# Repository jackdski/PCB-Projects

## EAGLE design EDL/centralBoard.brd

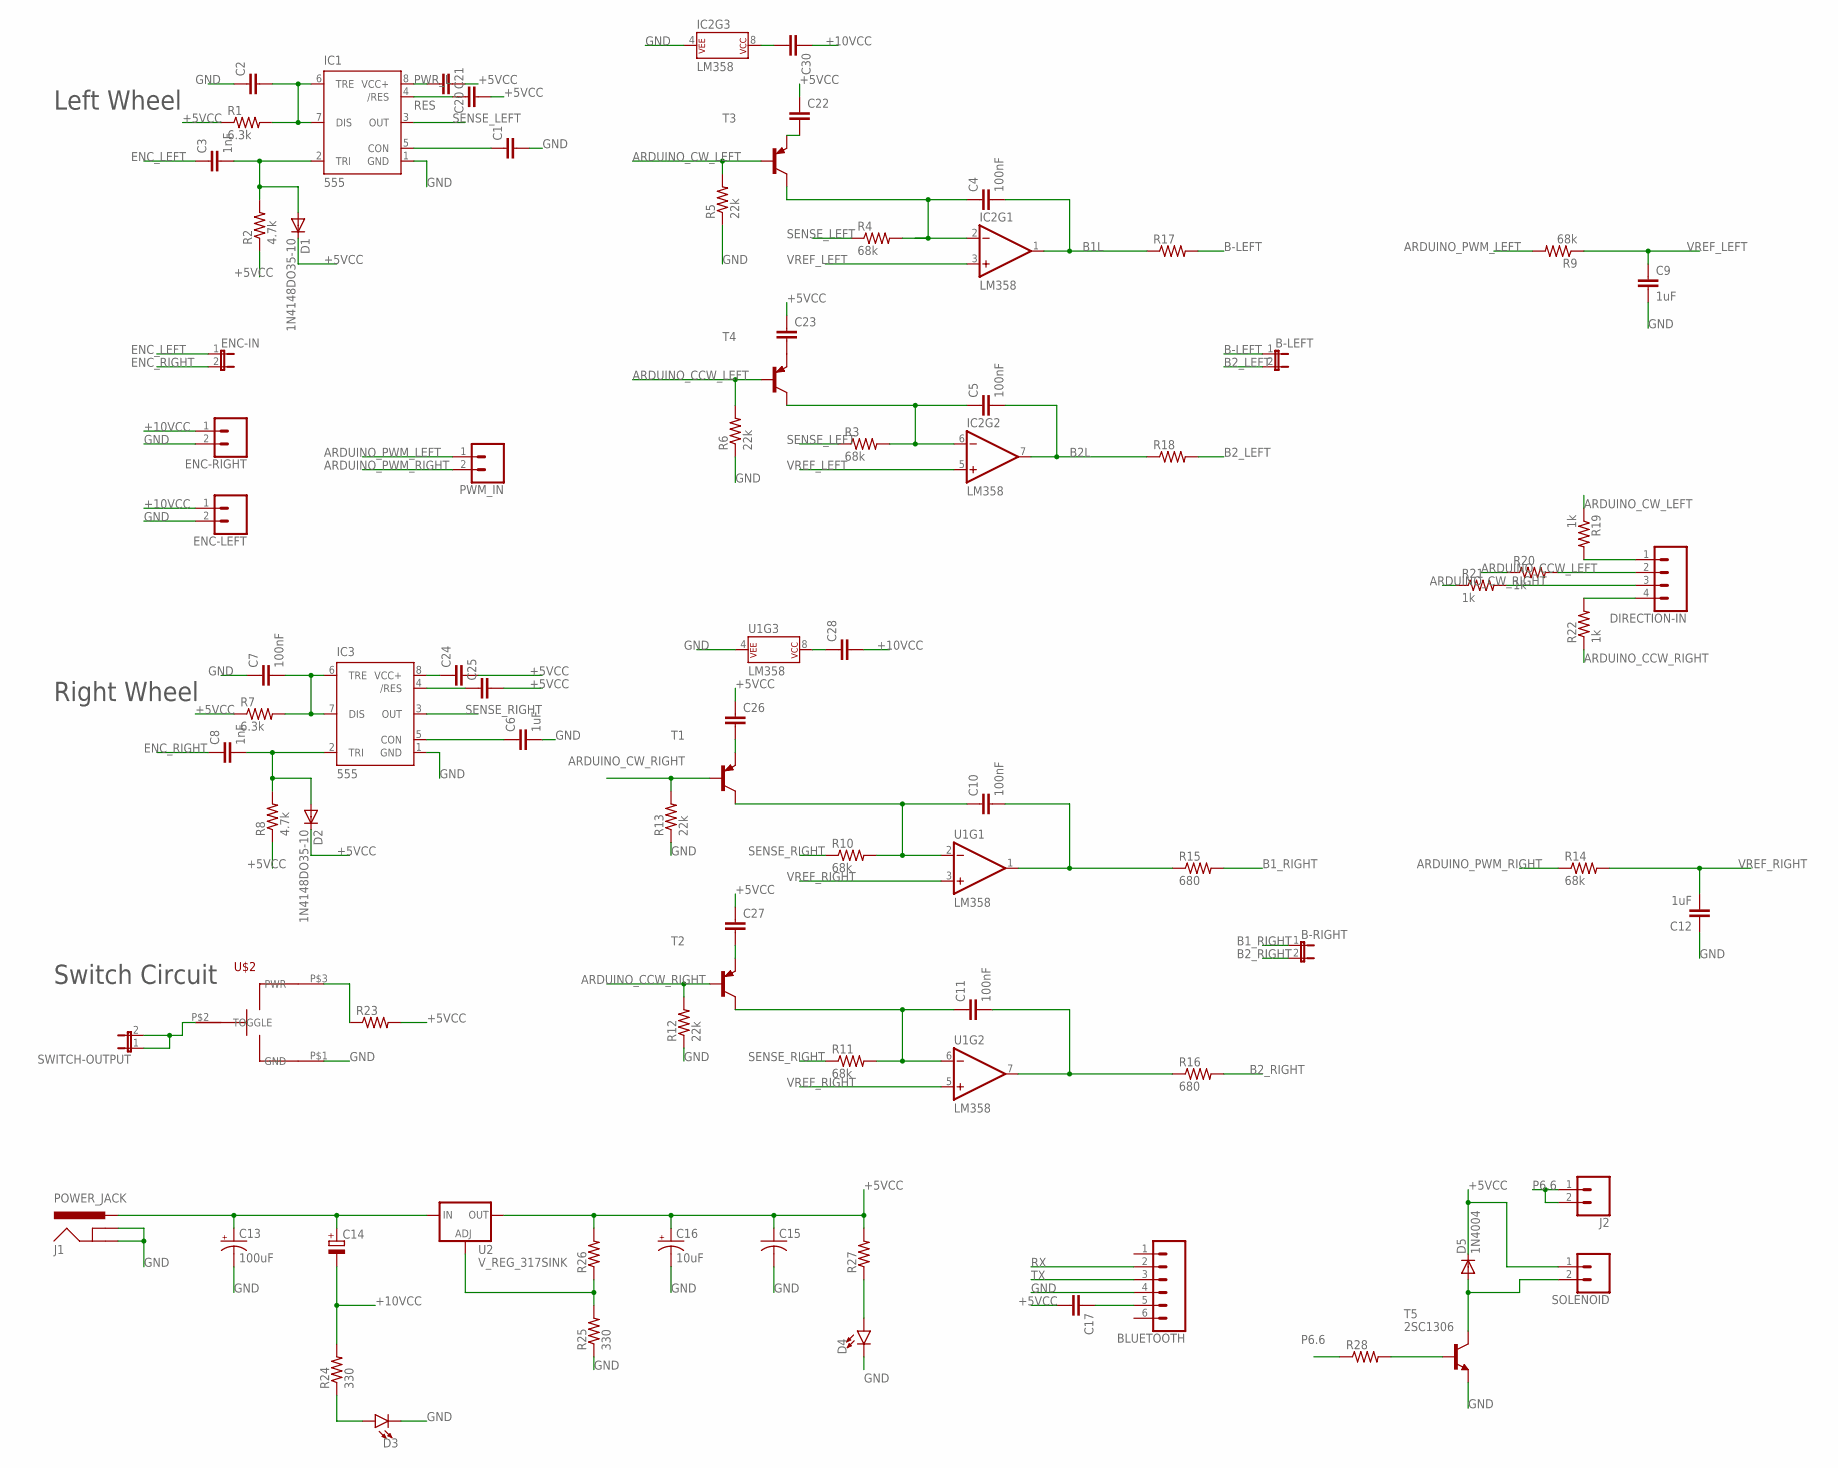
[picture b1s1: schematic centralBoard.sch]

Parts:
B-LEFT: JUMPER-2PTH; 1X02
B-RIGHT: JUMPER-2PTH; 1X02
BLUETOOTH: CONN_06SILK_FEMALE_PTH; 1X06
C1, C2, C20, C21, C22, C23, C24, C25, C26, C27, C28, C30: C5/2.5; C5B2.5
C3, C8: 1nF; C5B2.5
C4, C5, C7, C10, C11: 100nF; C5B2.5
C6, C9, C12: 1uF; C5B2.5
C13: 100uF; CPOL-RADIAL-2.5MM-6.5MM
C14: CPOL-EUE5-6; E5-6
C15: C-US050-030X075; C050-030X075
C16: 10uF; CPOL-RADIAL-2.5MM-5MM
C17: C5/3; C5B3
D1, D2: 1N4148DO35-10; DO35-10
D3, D4: LED-RED1206; LED-1206
D5: 1N4004; DO41-10
DIRECTION-IN: CONN_04; 1X04
ENC-IN: JUMPER-2PTH; 1X02
ENC-LEFT: CONN_02; 1X02
ENC-RIGHT: CONN_02; 1X02
IC1, IC3: 555; DIP08-KIT
IC2: LM358; DIP08
J1: POWER_JACK; POWER_JACK_PTH
J2: CONN_02; 1X02
PWM_IN: CONN_02LOCK; 1X02_LOCK
R1, R7: 6.3k; 0207/10
R2, R8: 4.7k; 0207/10
R3, R4, R9, R10, R11, R14: 68k; 0207/10
R5, R6, R12, R13: 22k; 0207/10
R15, R16: 680; 0207/10
R17, R18, R23, R26, R27, R28: R-US_0207/10; 0207/10
R19, R20, R21, R22: 1k; 0207/10
R24, R25: 330; 0207/10
SOLENOID: CONN_02; 1X02
SWITCH-OUTPUT: JUMPER-2PTH; 1X02
T1, T2, T3, T4: 2N4126-PNP-TO92-CBE; TO92-CBE
T5: 2SC1306; TO220BV
U1: LM358; DIP08
U2: V_REG_317SINK; TO220-ADJ
U$2: SWITCH

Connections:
+5VCC: C15.1, C16.1 (+), C17.2, C20.1, C21.2, C22.1, C23.1, C24.2, C25.2, C26.1, C27.1, D1.C, D2.C, D5.C, R1.1, R2.1, R7.1, R8.1, R23.2, R26.2, R27.2, SOLENOID.1, U2.OUT
+10VCC: C14.-, C28.2, C30.1, ENC-LEFT.1, ENC-RIGHT.1, R24.2
ARDUINO_CCW_LEFT: R6.2, R20.1, T4.B
ARDUINO_CCW_RIGHT: R12.2, R22.1, T2.B
ARDUINO_CW_LEFT: R5.2, R19.1, T3.B
ARDUINO_CW_RIGHT: R13.2, R21.1, T1.B
ARDUINO_PWM_LEFT: PWM_IN.1, R9.2
ARDUINO_PWM_RIGHT: PWM_IN.2, R14.1
B1L: C4.2, IC2.1 (OUT), R17.1
B1R: C10.2, R15.1, U1.1 (OUT)
B1_RIGHT: B-RIGHT.1, R15.2
B2L: C5.2, IC2.7 (OUT), R18.1
B2R: C11.2, R16.1, U1.7 (OUT)
B2_LEFT: B-LEFT.2, R18.2
B2_RIGHT: B-RIGHT.2, R16.2
B-LEFT: B-LEFT.1, R17.2
ENC_LEFT: C3.1, ENC-IN.1
ENC_RIGHT: C8.1, ENC-IN.2
GND: BLUETOOTH.4, C1.2, C2.1, C6.2, C7.1, C9.2, C12.1, C13.2 (-), C15.2, C16.2 (-), D3.C, D4.C, ENC-LEFT.2, ENC-RIGHT.2, IC1.1 (GND), IC2.4 (P$V-), IC3.1 (GND), J1.GND, J1.GNDBREAK, R5.1, R6.1, R12.1, R13.1, R25.1, T5.3 (E), U1.4 (P$V-), U$2.P$1 (GND)
unnamed: C1.1, IC1.5 (CON)
unnamed: C22.2, T3.E
unnamed: C4.1, IC2.2 (-IN), R4.2, T3.C
unnamed: C2.2, IC1.6 (TRE), IC1.7 (DIS), R1.2
unnamed: C23.2, T4.E
unnamed: C5.1, IC2.6 (-IN), R3.2, T4.C
unnamed: C3.2, D1.A, IC1.2 (TRI), R2.2
unnamed: C10.1, R10.2, T1.C, U1.2 (-IN)
unnamed: C24.1, IC3.8 (VCC+)
unnamed: C26.2, T1.E
unnamed: C6.1, IC3.5 (CON)
unnamed: C7.2, IC3.6 (TRE), IC3.7 (DIS), R7.2
unnamed: C8.2, D2.A, IC3.2 (TRI), R8.2
unnamed: C11.1, R11.2, T2.C, U1.6 (-IN)
unnamed: C30.2, IC2.8 (P$V+)
unnamed: DIRECTION-IN.1, R19.2
unnamed: DIRECTION-IN.2, R20.2
unnamed: DIRECTION-IN.3, R21.2
unnamed: DIRECTION-IN.4, R22.2
unnamed: C27.2, T2.E
unnamed: C25.1, IC3.4 (/RES)
unnamed: C13.1 (+), C14.+, J1.PWR, U2.IN
unnamed: R23.1, U$2.P$3 (PWR)
unnamed: C28.1, U1.8 (P$V+)
unnamed: D4.A, R27.1
unnamed: R25.2, R26.1, U2.ADJ
unnamed: SWITCH-OUTPUT.1, SWITCH-OUTPUT.2, U$2.P$2 (TOGGLE)
unnamed: D3.A, R24.1
unnamed: BLUETOOTH.5, C17.1
unnamed: R28.2, T5.1 (B)
unnamed: D5.A, SOLENOID.2, T5.2 (C)
P6.6: J2.1, J2.2, R28.1
PWR_L: C20.2, IC1.8 (VCC+)
RES: C21.1, IC1.4 (/RES)
RX: BLUETOOTH.2
SENSE_LEFT: IC1.3 (OUT), R3.1, R4.1
SENSE_RIGHT: IC3.3 (OUT), R10.1, R11.1
TX: BLUETOOTH.3
VREF_LEFT: C9.1, IC2.3 (+IN), IC2.5 (+IN), R9.1
VREF_RIGHT: C12.2, R14.2, U1.3 (+IN), U1.5 (+IN)

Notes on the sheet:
Right Wheel
Left Wheel
Switch Circuit

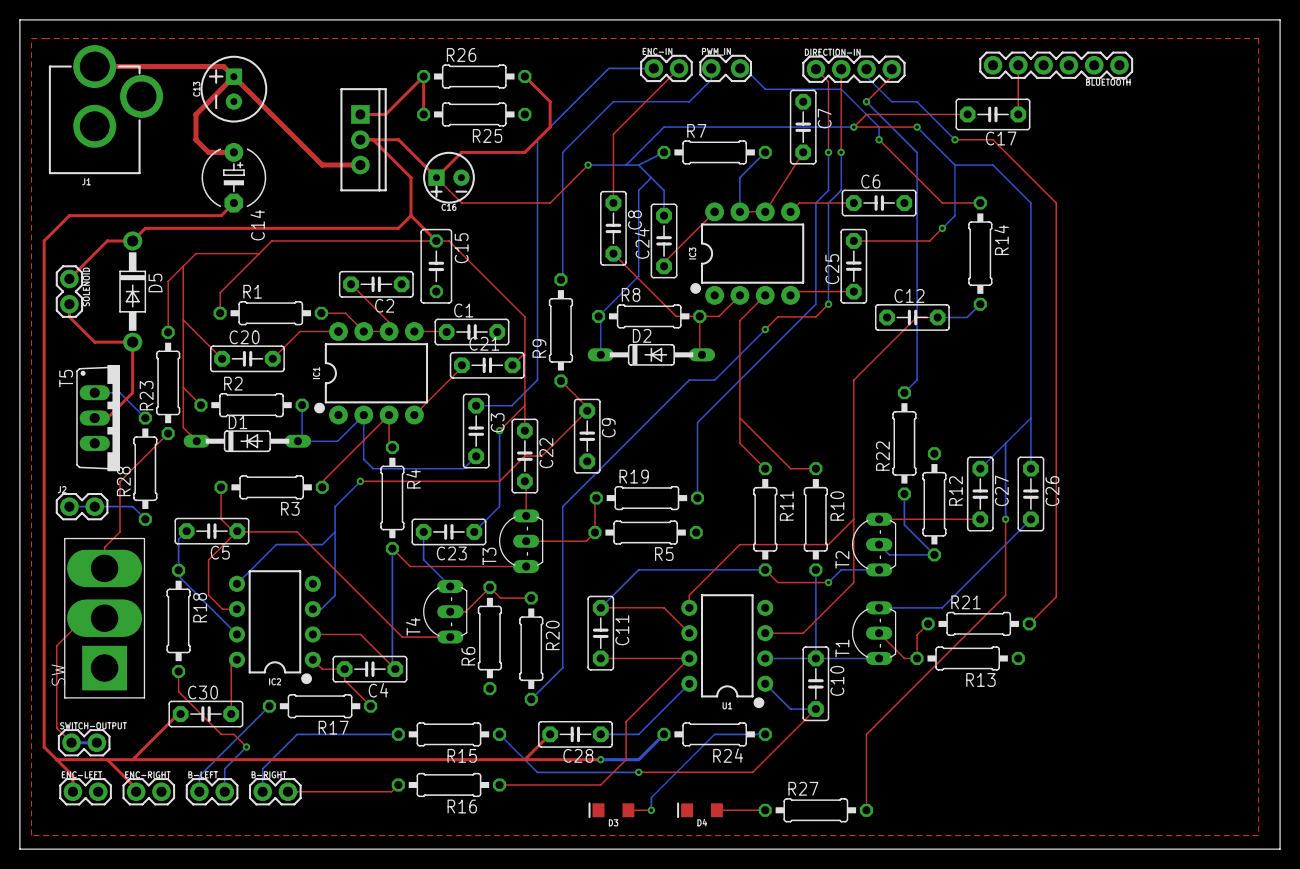
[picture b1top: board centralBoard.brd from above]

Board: 2 copper layers, 126.5 x 83.2 mm, 83 parts (0 on the bottom side), 57 nets.

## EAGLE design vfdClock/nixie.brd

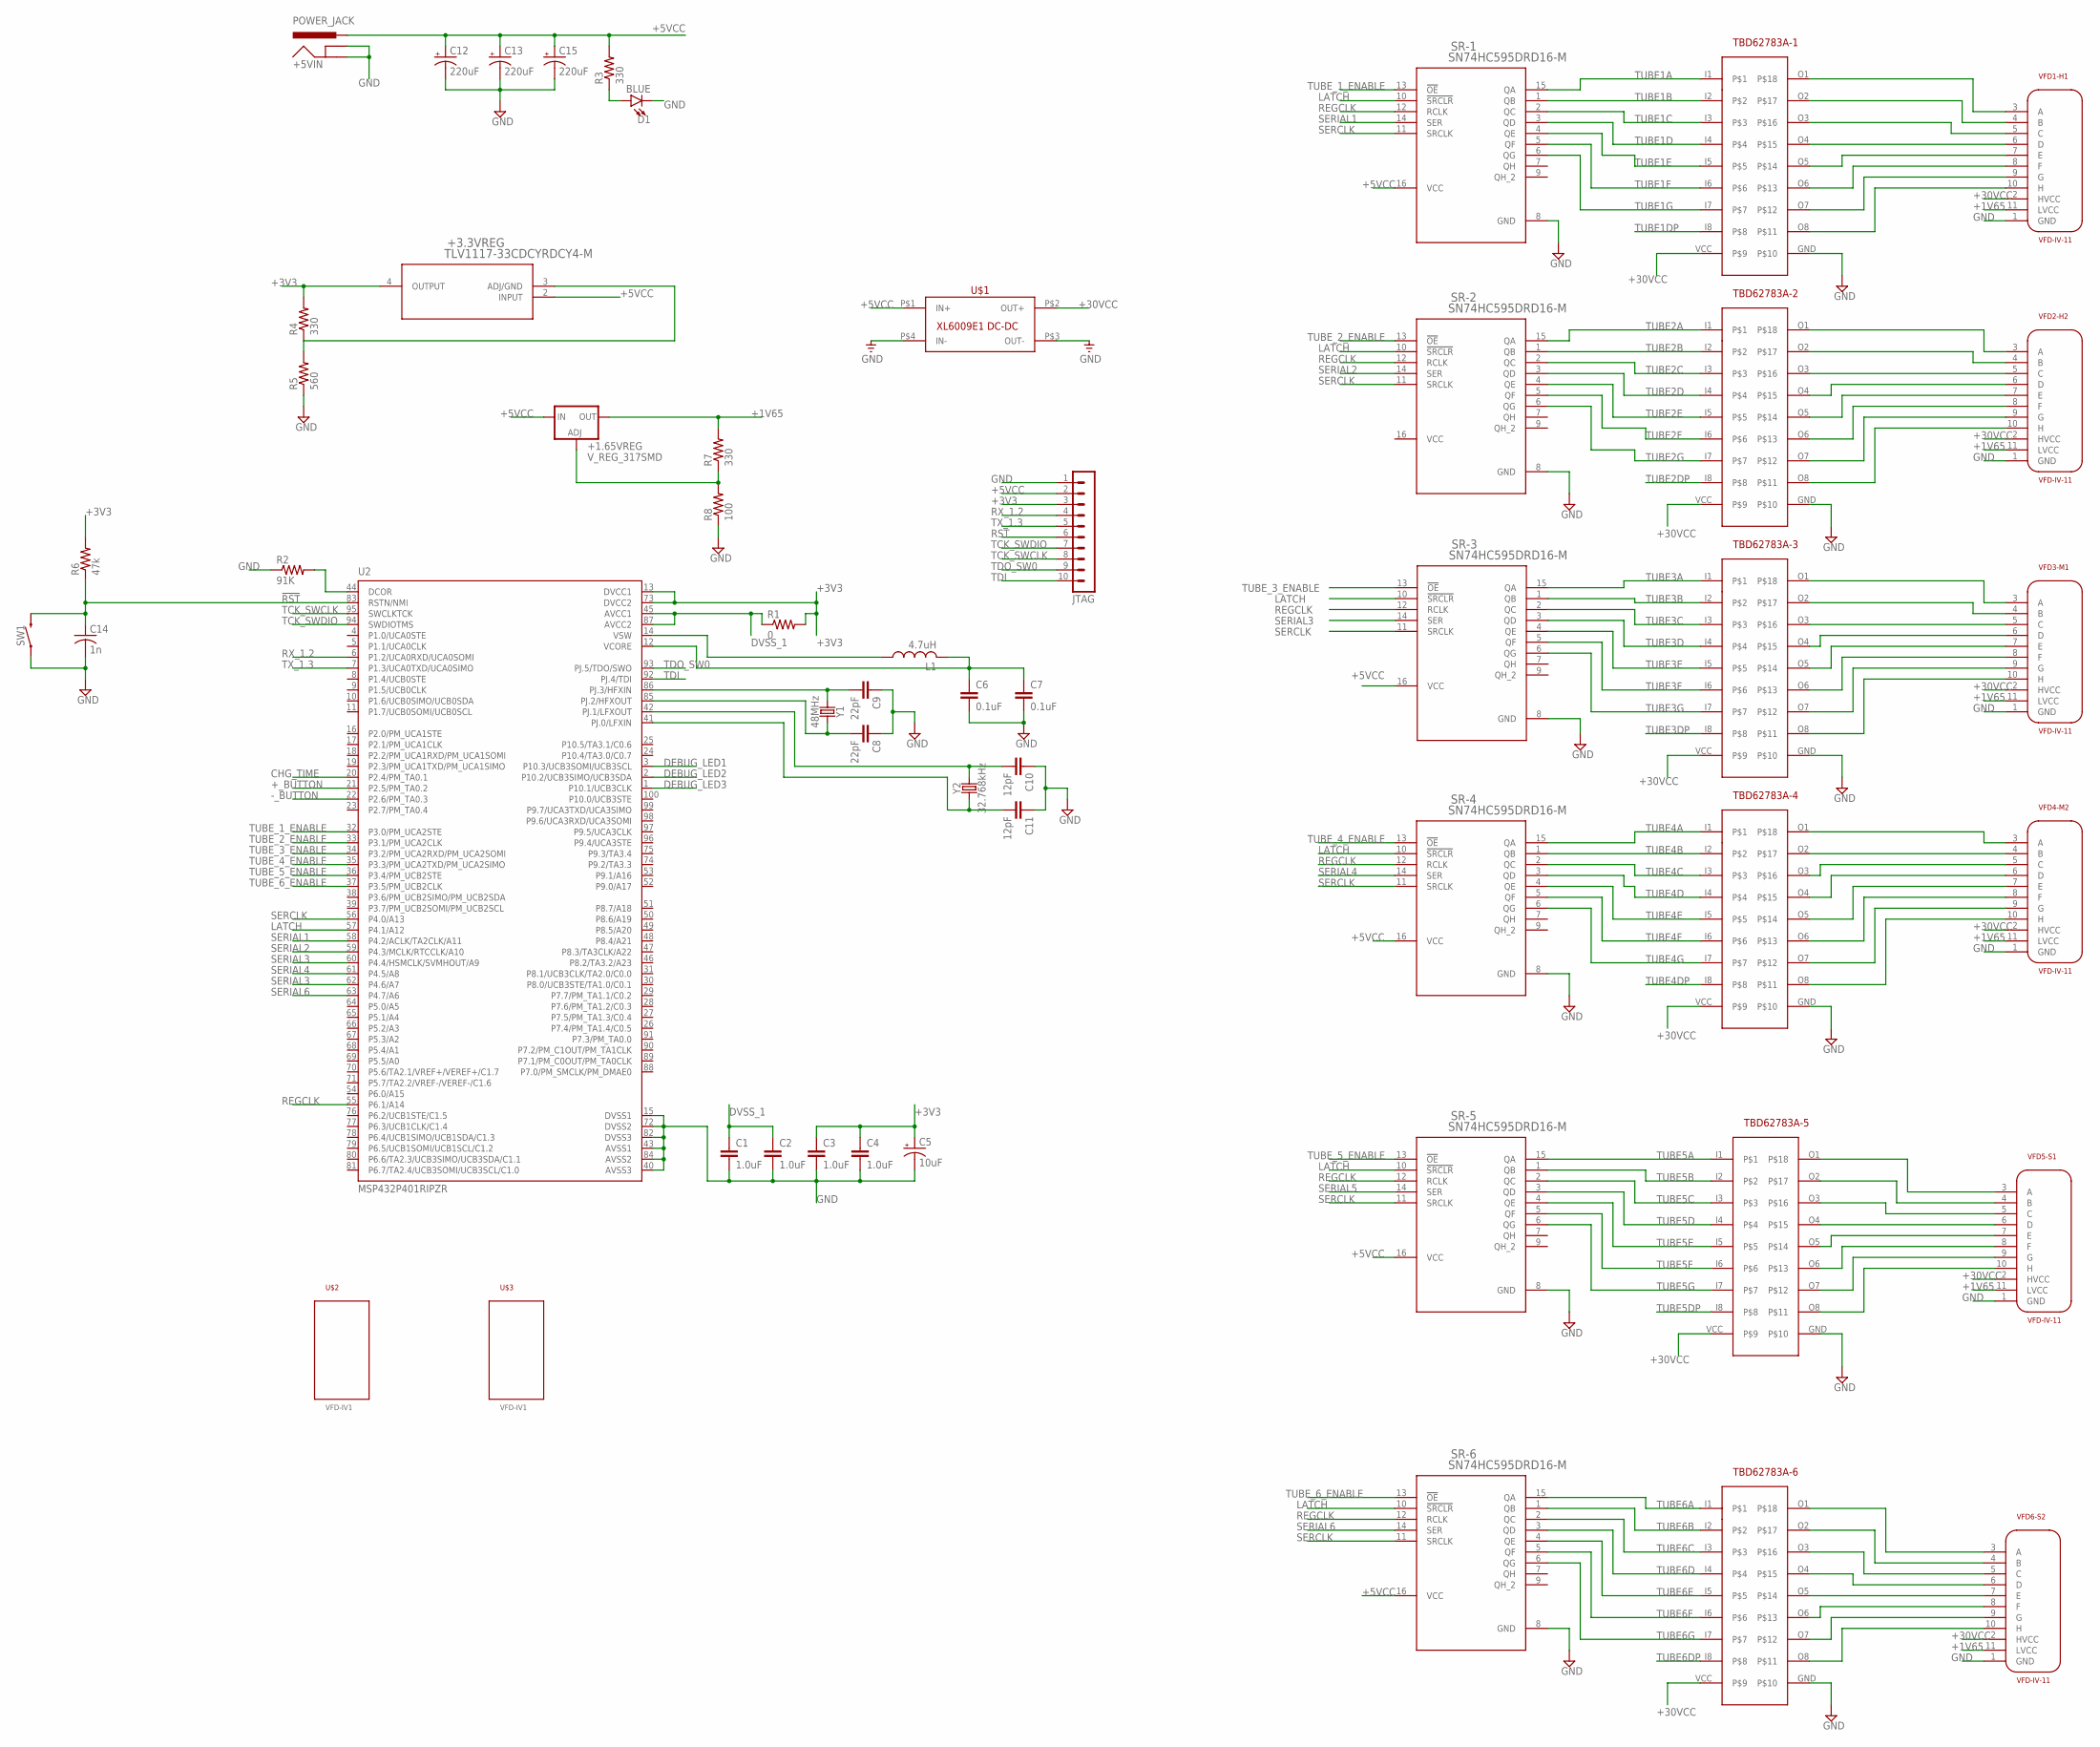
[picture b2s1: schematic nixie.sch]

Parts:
+1.65VREG: V_REG_317SMD; SOT223
+3.3VREG: TLV1117-33CDCYRDCY4-M; DCY4-M
+5VIN: POWER_JACK; POWER_JACK_PTH
C1, C2, C3, C4: 1.0uF; 0805
C5: 10uF; EIA3216
C6, C7: 0.1uF; 0603
C8, C9: 22pF; 0603
C10, C11: 12pF; 0603
C12, C13, C15: 220uF; E2-5
C14: 1n; C0805K
D1: BLUE; LED-1206
JTAG: MA10-1
L1: 4.7uH; L0603
R1: 0; MINI_MELF-0204W
R2: 91K; MINI_MELF-0204W
R3, R4, R7: 330; MINI_MELF-0204W
R5: 560; MINI_MELF-0204W
R6: 47k; MINI_MELF-0204W
R8: 100; MINI_MELF-0204W
SR-1, SR-2, SR-3, SR-4, SR-5, SR-6: SN74HC595DRD16-M; D16-M
SW1: MOMENTARY-SWITCH-SPST-SMD-6.2MM-TALL; TACTILE_SWITCH_SMD_6.2MM_TALL
TBD62783A-1, TBD62783A-2, TBD62783A-3, TBD62783A-4, TBD62783A-5, TBD62783A-6: TBD62783AFG
U2: MSP432P401RIPZR; QFP50P1600X1600X160-100N
U$1: XL6009E1
U$2, U$3: VFD-IV-1; VFD-IV1
VFD1-H1, VFD2-H2, VFD3-M1, VFD4-M2, VFD5-S1, VFD6-S2: VFD-IV-11; VFD-IV11
Y1: 48MHz; CRYSTAL-SMD-3.2X2.5MM
Y2: 32.768kHz; CRYSTAL-SMD-3.2X1.5MM

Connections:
!RST: C14.1, R6.1, SW1.B2 (2), U2.83 (RSTN/NMI)
+1V65: +1.65VREG.2 (OUT), R7.2, VFD1-H1.11 (LVCC), VFD2-H2.11 (LVCC), VFD3-M1.11 (LVCC), VFD4-M2.11 (LVCC), VFD5-S1.11 (LVCC), VFD6-S2.11 (LVCC)
+3V3: +3.3VREG.4 (OUTPUT), C3.1, C4.1, C5.+, JTAG.3, R1.2, R4.2, R6.2, U2.13 (DVCC1), U2.73 (DVCC2)
+5VCC: +1.65VREG.3 (IN), +3.3VREG.2 (INPUT), +5VIN.PWR, C12.+, C13.+, C15.+, JTAG.2, R3.2, SR-1.16 (VCC), SR-3.16 (VCC), SR-4.16 (VCC), SR-5.16 (VCC), SR-6.16 (VCC), U$1.P$1 (IN+)
+30VCC: TBD62783A-1.VCC, TBD62783A-2.VCC, TBD62783A-3.VCC, TBD62783A-4.VCC, TBD62783A-5.VCC, TBD62783A-6.VCC, U$1.P$2 (OUT+), VFD1-H1.2 (HVCC), VFD2-H2.2 (HVCC), VFD3-M1.2 (HVCC), VFD4-M2.2 (HVCC), VFD5-S1.2 (HVCC), VFD6-S2.2 (HVCC)
+_BUTTON: U2.21 (P2.5/PM_TA0.2)
-_BUTTON: U2.22 (P2.6/PM_TA0.3)
CHG_TIME: U2.20 (P2.4/PM_TA0.1)
DEBUG_LED1: U2.3 (P10.3/UCB3SOMI/UCB3SCL)
DEBUG_LED2: U2.2 (P10.2/UCB3SIMO/UCB3SDA)
DEBUG_LED3: U2.1 (P10.1/UCB3CLK)
DVSS_1: C1.1, C2.1, R1.1, U2.45 (AVCC1), U2.87 (AVCC2)
GND: +5VIN.GND, +5VIN.GNDBREAK, C1.2, C2.2, C3.2, C4.2, C5.-, C6.2, C7.2, C8.1, C9.1, C10.1, C11.1, C12.-, C13.-, C14.2, C15.-, D1.C, JTAG.1, R2.1, R5.1, R8.1, SR-1.8 (GND), SR-2.8 (GND), SR-3.8 (GND), SR-4.8 (GND), SR-5.8 (GND), SR-6.8 (GND), SW1.A2 (1), TBD62783A-1.GND, TBD62783A-2.GND, TBD62783A-3.GND, TBD62783A-4.GND, TBD62783A-5.GND, TBD62783A-6.GND, U2.15 (DVSS1), U2.40 (AVSS3), U2.43 (AVSS1), U2.72 (DVSS2), U2.82 (DVSS3), U2.84 (AVSS2), U$1.P$3 (OUT-), U$1.P$4 (IN-), VFD1-H1.1 (GND), VFD2-H2.1 (GND), VFD3-M1.1 (GND), VFD4-M2.1 (GND), VFD5-S1.1 (GND), VFD6-S2.1 (GND)
LATCH: SR-1.10 (!SRCLR), SR-2.10 (!SRCLR), SR-3.10 (!SRCLR), SR-4.10 (!SRCLR), SR-5.10 (!SRCLR), SR-6.10 (!SRCLR), U2.57 (P4.1/A12)
unnamed: L1.1, U2.14 (VSW)
unnamed: C8.2, U2.85 (PJ.2/HFXOUT), Y1.3 (2)
unnamed: C6.1, C7.1, L1.2, U2.12 (VCORE)
unnamed: C9.2, U2.86 (PJ.3/HFXIN), Y1.1
unnamed: C10.2, U2.42 (PJ.1/LFXOUT), Y2.P$2 (2)
unnamed: C11.2, U2.41 (PJ.0/LFXIN), Y2.P$1 (1)
unnamed: R2.2, U2.44 (DCOR)
unnamed: TBD62783A-1.O1, VFD1-H1.3 (A)
unnamed: TBD62783A-1.O2, VFD1-H1.4 (B)
unnamed: TBD62783A-1.O3, VFD1-H1.5 (C)
unnamed: TBD62783A-1.O4, VFD1-H1.6 (D)
unnamed: TBD62783A-1.O5, VFD1-H1.7 (E)
unnamed: TBD62783A-1.O6, VFD1-H1.8 (F)
unnamed: TBD62783A-1.O7, VFD1-H1.9 (G)
unnamed: TBD62783A-1.O8, VFD1-H1.10 (H)
unnamed: TBD62783A-2.O1, VFD2-H2.3 (A)
unnamed: TBD62783A-2.O2, VFD2-H2.4 (B)
unnamed: TBD62783A-2.O3, VFD2-H2.5 (C)
unnamed: TBD62783A-2.O4, VFD2-H2.6 (D)
unnamed: TBD62783A-2.O5, VFD2-H2.7 (E)
unnamed: TBD62783A-2.O6, VFD2-H2.8 (F)
unnamed: TBD62783A-2.O7, VFD2-H2.9 (G)
unnamed: TBD62783A-2.O8, VFD2-H2.10 (H)
unnamed: TBD62783A-5.O1, VFD5-S1.3 (A)
unnamed: TBD62783A-5.O2, VFD5-S1.4 (B)
unnamed: TBD62783A-3.O1, VFD3-M1.3 (A)
unnamed: TBD62783A-3.O2, VFD3-M1.4 (B)
unnamed: TBD62783A-3.O3, VFD3-M1.5 (C)
unnamed: TBD62783A-3.O4, VFD3-M1.6 (D)
unnamed: TBD62783A-3.O5, VFD3-M1.7 (E)
unnamed: TBD62783A-3.O6, VFD3-M1.8 (F)
unnamed: TBD62783A-3.O7, VFD3-M1.9 (G)
unnamed: TBD62783A-3.O8, VFD3-M1.10 (H)
unnamed: TBD62783A-4.O1, VFD4-M2.3 (A)
unnamed: TBD62783A-4.O2, VFD4-M2.4 (B)
unnamed: TBD62783A-4.O3, VFD4-M2.5 (C)
unnamed: TBD62783A-4.O4, VFD4-M2.6 (D)
unnamed: TBD62783A-4.O5, VFD4-M2.7 (E)
unnamed: TBD62783A-4.O6, VFD4-M2.8 (F)
unnamed: TBD62783A-4.O7, VFD4-M2.9 (G)
unnamed: TBD62783A-4.O8, VFD4-M2.10 (H)
unnamed: TBD62783A-6.O1, VFD6-S2.3 (A)
unnamed: TBD62783A-6.O2, VFD6-S2.4 (B)
unnamed: TBD62783A-6.O3, VFD6-S2.5 (C)
unnamed: TBD62783A-6.O4, VFD6-S2.6 (D)
unnamed: TBD62783A-6.O5, VFD6-S2.7 (E)
unnamed: TBD62783A-6.O6, VFD6-S2.8 (F)
unnamed: TBD62783A-6.O7, VFD6-S2.9 (G)
unnamed: TBD62783A-6.O8, VFD6-S2.10 (H)
unnamed: TBD62783A-5.O3, VFD5-S1.5 (C)
unnamed: TBD62783A-5.O4, VFD5-S1.6 (D)
unnamed: TBD62783A-5.O5, VFD5-S1.7 (E)
unnamed: TBD62783A-5.O6, VFD5-S1.8 (F)
unnamed: TBD62783A-5.O7, VFD5-S1.9 (G)
unnamed: TBD62783A-5.O8, VFD5-S1.10 (H)
unnamed: D1.A, R3.1
unnamed: +1.65VREG.1 (ADJ), R7.1, R8.2
unnamed: +3.3VREG.3 (ADJ/GND), R4.1, R5.2
REGCLK: SR-1.12 (RCLK), SR-2.12 (RCLK), SR-3.12 (RCLK), SR-4.12 (RCLK), SR-5.12 (RCLK), SR-6.12 (RCLK), U2.55 (P6.1/A14)
RST: JTAG.6
RX_1.2: JTAG.4, U2.6 (P1.2/UCA0RXD/UCA0SOMI)
SERCLK: SR-1.11 (SRCLK), SR-2.11 (SRCLK), SR-3.11 (SRCLK), SR-4.11 (SRCLK), SR-5.11 (SRCLK), SR-6.11 (SRCLK), U2.56 (P4.0/A13)
SERIAL1: SR-1.14 (SER), U2.58 (P4.2/ACLK/TA2CLK/A11)
SERIAL2: SR-2.14 (SER), U2.59 (P4.3/MCLK/RTCCLK/A10)
SERIAL3: SR-3.14 (SER), U2.60 (P4.4/HSMCLK/SVMHOUT/A9), U2.62 (P4.6/A7)
SERIAL4: SR-4.14 (SER), U2.61 (P4.5/A8)
SERIAL5: SR-5.14 (SER)
SERIAL6: SR-6.14 (SER), U2.63 (P4.7/A6)
TCK_SWCLK: JTAG.8, U2.95 (SWCLKTCK)
TCK_SWDIO: JTAG.7, U2.94 (SWDIOTMS)
TDI: JTAG.10, U2.92 (PJ.4/TDI)
TDO_SW0: JTAG.9, U2.93 (PJ.5/TDO/SWO)
TUBE1A: SR-1.15 (QA), TBD62783A-1.I1
TUBE1B: SR-1.1 (QB), TBD62783A-1.I2
TUBE1C: SR-1.2 (QC), TBD62783A-1.I3
TUBE1D: SR-1.3 (QD), TBD62783A-1.I4
TUBE1DP: TBD62783A-1.I8
TUBE1E: SR-1.4 (QE), TBD62783A-1.I5
TUBE1F: SR-1.5 (QF), TBD62783A-1.I6
TUBE1G: SR-1.6 (QG), TBD62783A-1.I7
TUBE2A: SR-2.15 (QA), TBD62783A-2.I1
TUBE2B: SR-2.1 (QB), TBD62783A-2.I2
TUBE2C: SR-2.2 (QC), TBD62783A-2.I3
TUBE2D: SR-2.3 (QD), TBD62783A-2.I4
TUBE2DP: TBD62783A-2.I8
TUBE2E: SR-2.4 (QE), TBD62783A-2.I5
TUBE2F: SR-2.5 (QF), TBD62783A-2.I6
TUBE2G: SR-2.6 (QG), TBD62783A-2.I7
TUBE3A: SR-3.15 (QA), TBD62783A-3.I1
TUBE3B: SR-3.1 (QB), TBD62783A-3.I2
TUBE3C: SR-3.2 (QC), TBD62783A-3.I3
TUBE3D: SR-3.3 (QD), TBD62783A-3.I4
TUBE3DP: TBD62783A-3.I8
TUBE3E: SR-3.4 (QE), TBD62783A-3.I5
TUBE3F: SR-3.5 (QF), TBD62783A-3.I6
TUBE3G: SR-3.6 (QG), TBD62783A-3.I7
TUBE4A: SR-4.15 (QA), TBD62783A-4.I1
TUBE4B: SR-4.1 (QB), TBD62783A-4.I2
TUBE4C: SR-4.2 (QC), TBD62783A-4.I3
TUBE4D: SR-4.3 (QD), TBD62783A-4.I4
TUBE4DP: TBD62783A-4.I8
TUBE4E: SR-4.4 (QE), TBD62783A-4.I5
TUBE4F: SR-4.5 (QF), TBD62783A-4.I6
TUBE4G: SR-4.6 (QG), TBD62783A-4.I7
TUBE5A: SR-5.15 (QA), TBD62783A-5.I1
TUBE5B: SR-5.1 (QB), TBD62783A-5.I2
TUBE5C: SR-5.2 (QC), TBD62783A-5.I3
TUBE5D: SR-5.3 (QD), TBD62783A-5.I4
TUBE5DP: TBD62783A-5.I8
TUBE5E: SR-5.4 (QE), TBD62783A-5.I5
TUBE5F: SR-5.5 (QF), TBD62783A-5.I6
TUBE5G: SR-5.6 (QG), TBD62783A-5.I7
TUBE6A: SR-6.15 (QA), TBD62783A-6.I1
TUBE6B: SR-6.1 (QB), TBD62783A-6.I2
TUBE6C: SR-6.2 (QC), TBD62783A-6.I3
TUBE6D: SR-6.3 (QD), TBD62783A-6.I4
TUBE6DP: TBD62783A-6.I8
TUBE6E: SR-6.4 (QE), TBD62783A-6.I5
TUBE6F: SR-6.5 (QF), TBD62783A-6.I6
TUBE6G: SR-6.6 (QG), TBD62783A-6.I7
TUBE_1_ENABLE: SR-1.13 (!OE), U2.32 (P3.0/PM_UCA2STE)
TUBE_2_ENABLE: SR-2.13 (!OE), U2.33 (P3.1/PM_UCA2CLK)
TUBE_3_ENABLE: SR-3.13 (!OE), U2.34 (P3.2/PM_UCA2RXD/PM_UCA2SOMI)
TUBE_4_ENABLE: SR-4.13 (!OE), U2.35 (P3.3/PM_UCA2TXD/PM_UCA2SIMO)
TUBE_5_ENABLE: SR-5.13 (!OE), U2.36 (P3.4/PM_UCB2STE)
TUBE_6_ENABLE: SR-6.13 (!OE), U2.37 (P3.5/PM_UCB2CLK)
TX_1.3: JTAG.5, U2.7 (P1.3/UCA0TXD/UCA0SIMO)
VCC: SR-2.16 (VCC)

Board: 2 copper layers, 54 parts (7 on the bottom side), 127 nets, no tracks yet.

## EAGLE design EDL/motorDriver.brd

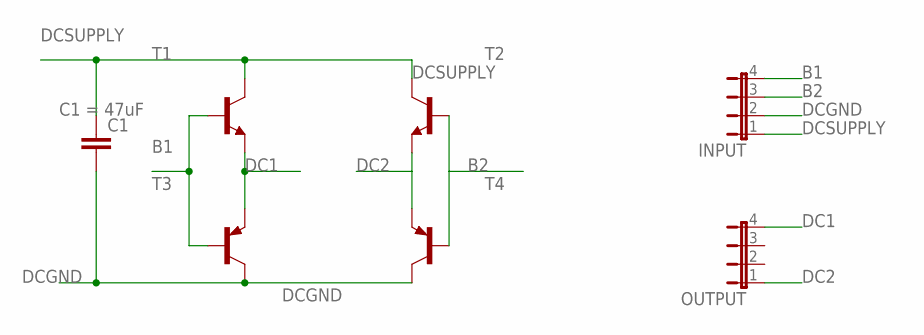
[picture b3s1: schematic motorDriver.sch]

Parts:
C1: C5/3.5; C5B3.5
INPUT: JP4E; JP4
OUTPUT: JP4E; JP4
T1, T2: -NPN-SOT93V; SOT93V
T3, T4: -PNP-SOT93V; SOT93V

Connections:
B1: INPUT.4, T1.B, T3.B
B2: INPUT.3, T2.B, T4.B
DC1: OUTPUT.4, T1.E, T3.E
DC2: OUTPUT.1, T2.E, T4.E
DCGND: C1.2, INPUT.2, T3.C, T4.C
DCSUPPLY: C1.1, INPUT.1, T1.C, T2.C

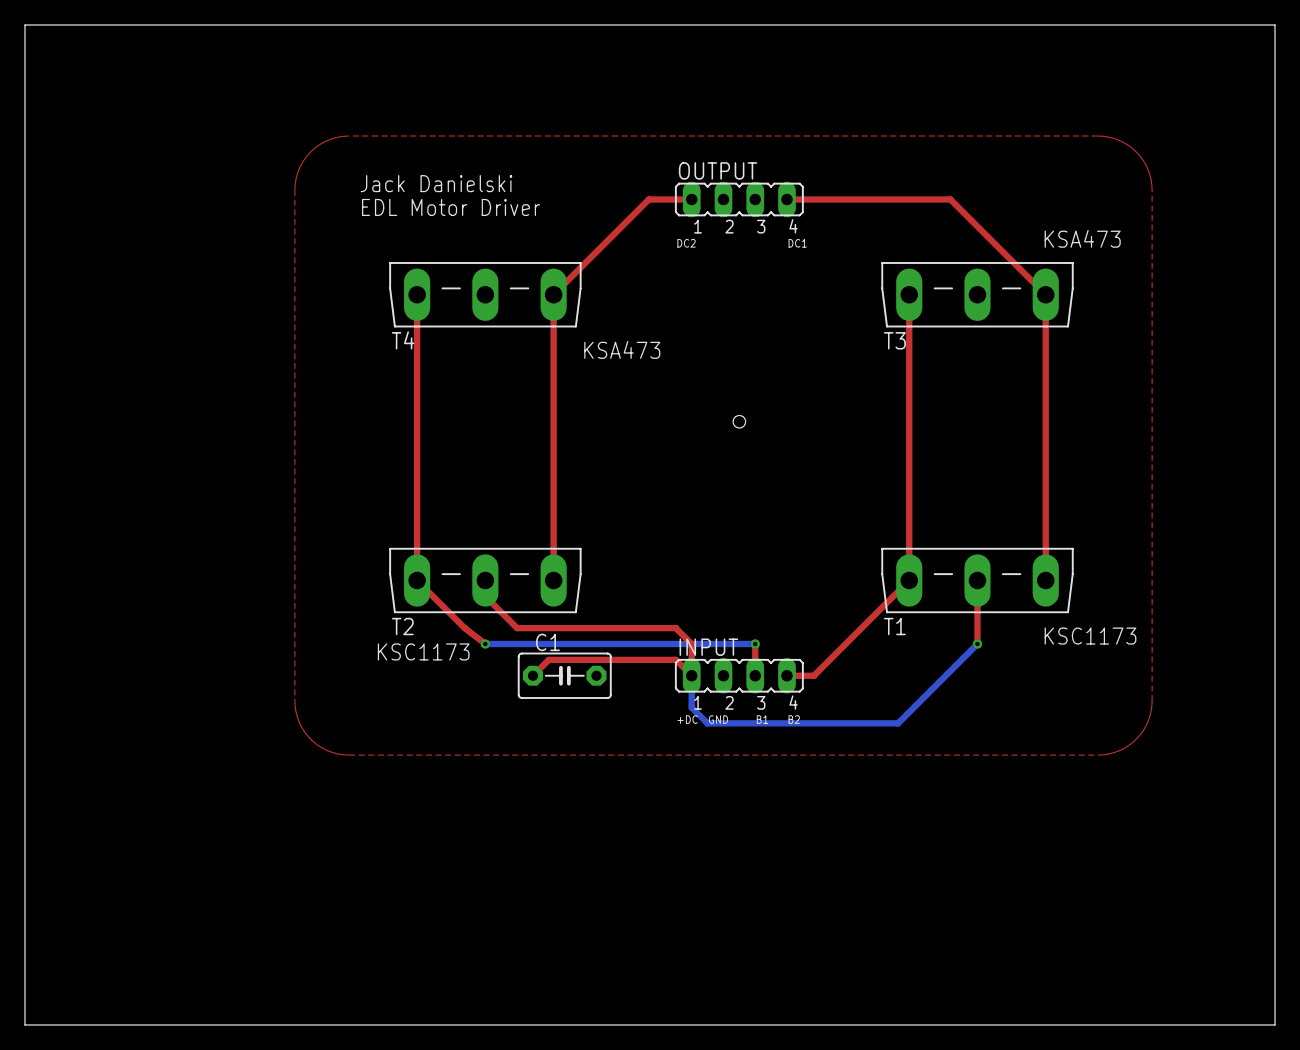
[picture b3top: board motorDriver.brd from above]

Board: 2 copper layers, 100.0 x 80.0 mm, 7 parts (0 on the bottom side), 6 nets.

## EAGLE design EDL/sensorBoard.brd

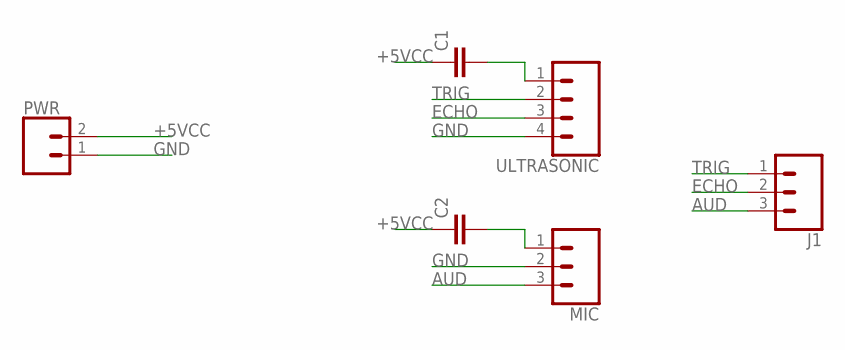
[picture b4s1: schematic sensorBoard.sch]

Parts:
C1, C2: C5/3; C5B3
J1: CONN_03; 1X03
MIC: CONN_03; 1X03
PWR: CONN_02; 1X02
ULTRASONIC: CONN_04; 1X04

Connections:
+5VCC: C1.1, C2.1, PWR.2
AUD: J1.3, MIC.3
ECHO: J1.2, ULTRASONIC.3
GND: MIC.2, PWR.1, ULTRASONIC.4
unnamed: C1.2, ULTRASONIC.1
unnamed: C2.2, MIC.1
TRIG: J1.1, ULTRASONIC.2

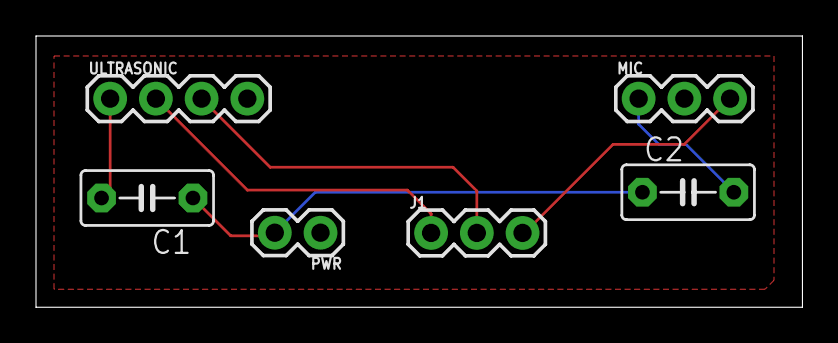
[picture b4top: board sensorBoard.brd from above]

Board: 2 copper layers, 42.6 x 15.1 mm, 6 parts (0 on the bottom side), 7 nets.

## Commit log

2018-08-22 Add two projects

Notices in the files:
parts and their libraries:
SparkFun-Retired: Licensing: Creative Commons ShareAlike 4.0 International - https://creativecommons.org/licenses/by-sa/4.0
